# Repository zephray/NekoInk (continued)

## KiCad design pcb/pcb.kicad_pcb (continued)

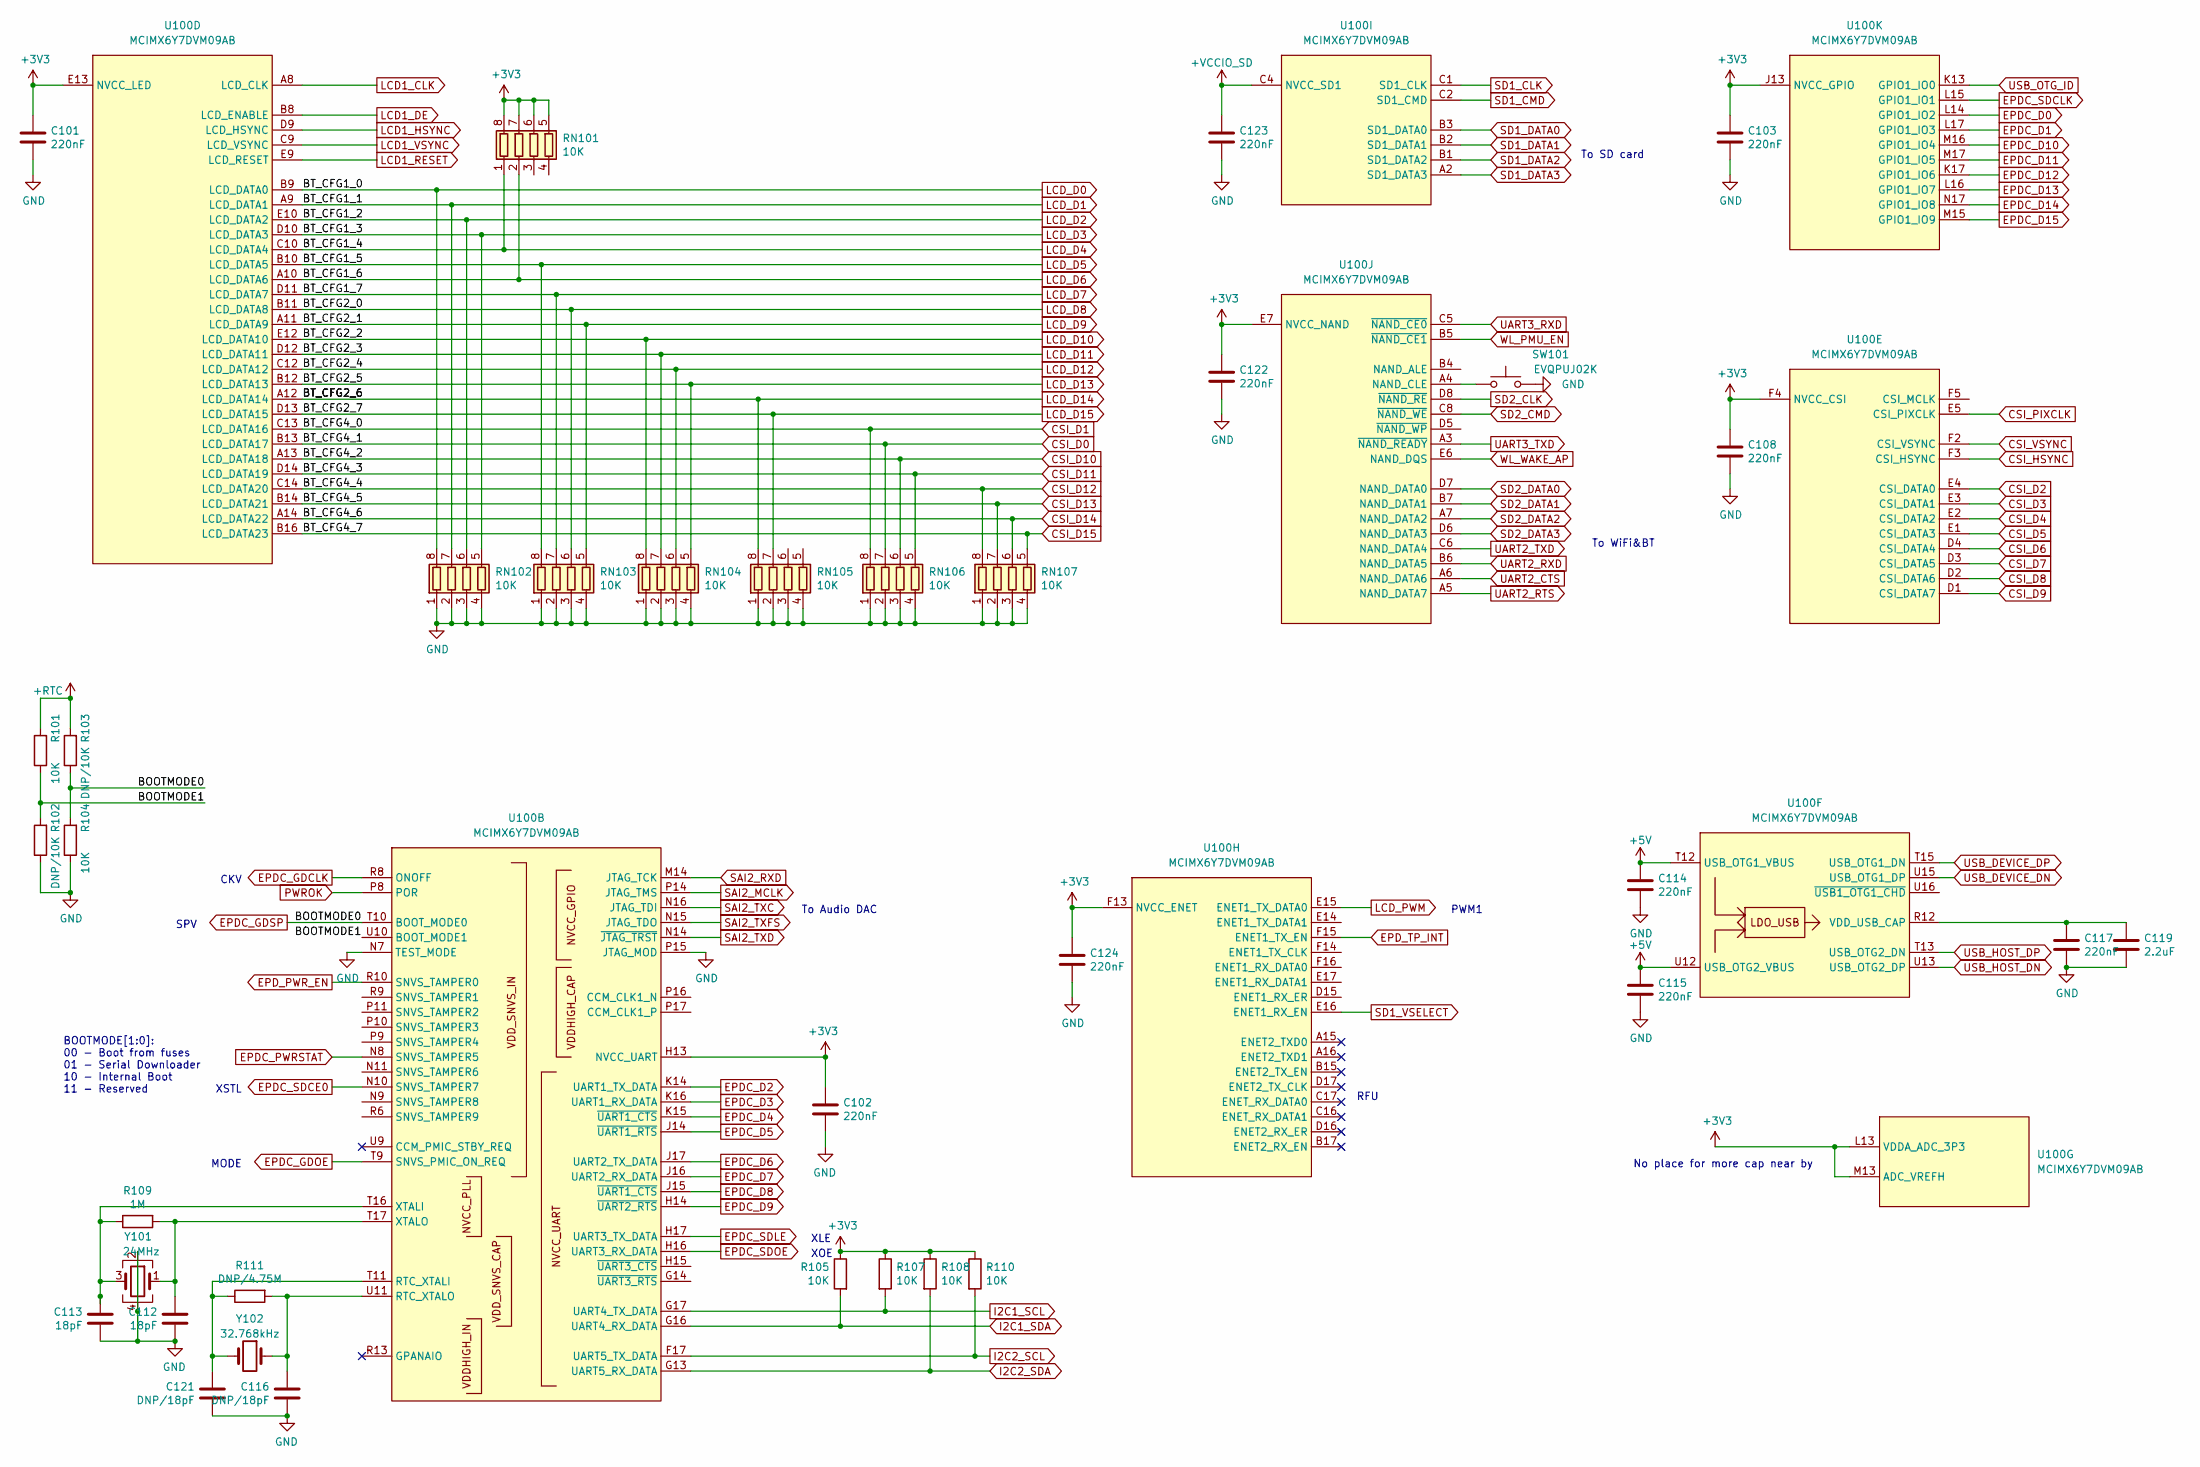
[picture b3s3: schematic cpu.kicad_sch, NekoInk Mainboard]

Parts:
C101, C102, C103, C108, C114, C115, C117, C122, C123, C124: 220nF; C_0402_1005Metric
C112, C113: 18pF; C_0402_1005Metric
C116, C121: DNP/18pF; C_0402_1005Metric
C119: 2.2uF; C_0402_1005Metric
R101, R104, R105, R107, R108, R110: 10K; R_0402_1005Metric
R102, R103: DNP/10K; R_0402_1005Metric
R109: 1M; R_0402_1005Metric
R111: DNP/4.75M; R_0402_1005Metric
RN101, RN102, RN103, RN104, RN105, RN106, RN107: 10K; R_Array_Convex_4x0402
SW101: EVQPUJ02K; Panasonic_EVQPUJ_EVQPUA
U100: MCIMX6Y7DVM09AB; BGA-289_17x17_14.0x14.0mm
Y101: 24MHz; Oscillator_SMD_Abracon_ASE-4Pin_3.2x2.5mm
Y102: 32.768kHz; Crystal_SMD_TXC_9HT11-2Pin_2.0x1.2mm_HandSoldering

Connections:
+5V: C114.1, C115.1, U100.T12 (USB_OTG1_VBUS), U100.U12 (USB_OTG2_VBUS); also elsewhere on the board
+RTC: R101.2, R103.2; also elsewhere on the board
/cpu/BOOTMODE1: R101.1, R102.2, U100.U10 (BOOT_MODE1)
CSI_D0: RN106.7 (R2.2), U100.B13 (LCD_DATA17); also elsewhere on the board
CSI_D1: RN106.8 (R1.2), U100.C13 (LCD_DATA16); also elsewhere on the board
CSI_D2: U100.E4 (CSI_DATA0); also elsewhere on the board
CSI_D3: U100.E3 (CSI_DATA1); also elsewhere on the board
CSI_D4: U100.E2 (CSI_DATA2); also elsewhere on the board
CSI_D5: U100.E1 (CSI_DATA3); also elsewhere on the board
CSI_D6: U100.D4 (CSI_DATA4); also elsewhere on the board
CSI_D7: U100.D3 (CSI_DATA5); also elsewhere on the board
CSI_D8: U100.D2 (CSI_DATA6); also elsewhere on the board
CSI_D9: U100.D1 (CSI_DATA7); also elsewhere on the board
CSI_D10: RN106.6 (R3.2), U100.A13 (LCD_DATA18); also elsewhere on the board
CSI_D11: RN106.5 (R4.2), U100.D14 (LCD_DATA19); also elsewhere on the board
CSI_D12: RN107.8 (R1.2), U100.C14 (LCD_DATA20); also elsewhere on the board
CSI_D13: RN107.7 (R2.2), U100.B14 (LCD_DATA21); also elsewhere on the board
CSI_D14: RN107.6 (R3.2), U100.A14 (LCD_DATA22); also elsewhere on the board
CSI_D15: RN107.5 (R4.2), U100.B16 (LCD_DATA23); also elsewhere on the board
CSI_HSYNC: U100.F3 (CSI_HSYNC); also elsewhere on the board
CSI_PIXCLK: U100.E5 (CSI_PIXCLK); also elsewhere on the board
CSI_VSYNC: U100.F2 (CSI_VSYNC); also elsewhere on the board
EPDC_D0: U100.L14 (GPIO1_IO2); also elsewhere on the board
EPDC_D1: U100.L17 (GPIO1_IO3); also elsewhere on the board
EPDC_D2: U100.K14 (UART1_TX_DATA); also elsewhere on the board
EPDC_D3: U100.K16 (UART1_RX_DATA); also elsewhere on the board
EPDC_D4: U100.K15 (~UART1_CTS); also elsewhere on the board
EPDC_D5: U100.J14 (~UART1_RTS); also elsewhere on the board
EPDC_D6: U100.J17 (UART2_TX_DATA); also elsewhere on the board
EPDC_D7: U100.J16 (UART2_RX_DATA); also elsewhere on the board
EPDC_D8: U100.J15 (~UART1_CTS); also elsewhere on the board
EPDC_D9: U100.H14 (~UART2_RTS); also elsewhere on the board
EPDC_D10: U100.M16 (GPIO1_IO4); also elsewhere on the board
EPDC_D11: U100.M17 (GPIO1_IO5); also elsewhere on the board
EPDC_D12: U100.K17 (GPIO1_IO6); also elsewhere on the board
EPDC_D13: U100.L16 (GPIO1_IO7); also elsewhere on the board
EPDC_D14: U100.N17 (GPIO1_IO8); also elsewhere on the board
EPDC_D15: U100.M15 (GPIO1_IO9); also elsewhere on the board
EPDC_GDCLK: U100.R8 (ONOFF); also elsewhere on the board
EPDC_GDOE: U100.T9 (SNVS_PMIC_ON_REQ); also elsewhere on the board
EPDC_GDSP: R103.1, R104.2, U100.T10 (BOOT_MODE0); also elsewhere on the board
EPDC_SDCE0: U100.N10 (SNVS_TAMPER7); also elsewhere on the board
EPDC_SDCLK: U100.L15 (GPIO1_IO1); also elsewhere on the board
EPDC_SDLE: U100.H17 (UART3_TX_DATA); also elsewhere on the board
EPDC_SDOE: U100.H16 (UART3_RX_DATA); also elsewhere on the board
EPD_PWR_EN: U100.R10 (SNVS_TAMPER0); also elsewhere on the board
EPD_TP_INT: U100.F15 (ENET1_TX_EN); also elsewhere on the board
GND: C101.2, C102.2, C103.2, C108.2, C112.2, C113.2, C114.2, C115.2, C116.2, C117.2, C119.2, C121.2, C122.2, C123.2, C124.2, R102.1, R104.1, RN102.1 (R1.1), RN102.2 (R2.1), RN102.3 (R3.1), RN102.4 (R4.1), RN103.1 (R1.1), RN103.2 (R2.1), RN103.3 (R3.1), RN103.4 (R4.1), RN104.1 (R1.1), RN104.2 (R2.1), RN104.3 (R3.1), RN104.4 (R4.1), RN105.1 (R1.1), RN105.2 (R2.1), RN105.3 (R3.1), RN105.4 (R4.1), RN106.1 (R1.1), RN106.2 (R2.1), RN106.3 (R3.1), RN106.4 (R4.1), RN107.1 (R1.1), RN107.2 (R2.1), RN107.3 (R3.1), RN107.4 (R4.1), SW101.2, U100.N7 (TEST_MODE), U100.P15 (JTAG_MOD), Y101.2, Y101.4; also elsewhere on the board
I2C1_SCL: R107.2, U100.G17 (UART4_TX_DATA); also elsewhere on the board
I2C1_SDA: R105.2, U100.G16 (UART4_RX_DATA); also elsewhere on the board
I2C2_SCL: R110.2, U100.F17 (UART5_TX_DATA)
I2C2_SDA: R108.2, U100.G13 (UART5_RX_DATA)
LCD1_CLK: U100.A8 (LCD_CLK); also elsewhere on the board
LCD1_DE: U100.B8 (LCD_ENABLE); also elsewhere on the board
LCD1_HSYNC: U100.D9 (LCD_HSYNC); also elsewhere on the board
LCD1_VSYNC: U100.C9 (LCD_VSYNC); also elsewhere on the board
LCD_D0: RN102.8 (R1.2), U100.B9 (LCD_DATA0); also elsewhere on the board
LCD_D1: RN102.7 (R2.2), U100.A9 (LCD_DATA1); also elsewhere on the board
LCD_D2: RN102.6 (R3.2), U100.E10 (LCD_DATA2); also elsewhere on the board
LCD_D3: RN102.5 (R4.2), U100.D10 (LCD_DATA3); also elsewhere on the board
LCD_D4: RN101.1 (R1.1), U100.C10 (LCD_DATA4); also elsewhere on the board
LCD_D5: RN103.8 (R1.2), U100.B10 (LCD_DATA5); also elsewhere on the board
LCD_D6: RN101.2 (R2.1), U100.A10 (LCD_DATA6); also elsewhere on the board
LCD_D7: RN103.7 (R2.2), U100.D11 (LCD_DATA7); also elsewhere on the board
LCD_D8: RN103.6 (R3.2), U100.B11 (LCD_DATA8); also elsewhere on the board
LCD_D9: RN103.5 (R4.2), U100.A11 (LCD_DATA9); also elsewhere on the board
LCD_D10: RN104.8 (R1.2), U100.E12 (LCD_DATA10); also elsewhere on the board
LCD_D11: RN104.7 (R2.2), U100.D12 (LCD_DATA11); also elsewhere on the board
LCD_D12: RN104.6 (R3.2), U100.C12 (LCD_DATA12); also elsewhere on the board
LCD_D13: RN104.5 (R4.2), U100.B12 (LCD_DATA13); also elsewhere on the board
LCD_D14: RN105.8 (R1.2), U100.A12 (LCD_DATA14); also elsewhere on the board
LCD_D15: RN105.7 (R2.2), U100.D13 (LCD_DATA15); also elsewhere on the board
LCD_PWM: U100.E15 (ENET1_TX_DATA0); also elsewhere on the board
unnamed: C112.1, R109.2, U100.T17 (XTALO), Y101.1
unnamed: C113.1, R109.1, U100.T16 (XTALI), Y101.3
unnamed: C116.1, R111.2, U100.U11 (RTC_XTALO), Y102.1
unnamed: C117.1, C119.1, U100.R12 (VDD_USB_CAP)
unnamed: C121.1, R111.1, U100.T11 (RTC_XTALI), Y102.2
unnamed: SW101.1, U100.A4 (NAND_CLE)
PWROK: U100.P8 (POR); also elsewhere on the board
SAI2_MCLK: U100.P14 (JTAG_TMS); also elsewhere on the board
SAI2_RXD: U100.M14 (JTAG_TCK); also elsewhere on the board
SAI2_TXC: U100.N16 (JTAG_TDI); also elsewhere on the board
SAI2_TXD: U100.N14 (~JTAG_TRST); also elsewhere on the board
SAI2_TXFS: U100.N15 (JTAG_TDO); also elsewhere on the board
SD1_CLK: U100.C1 (SD1_CLK); also elsewhere on the board
SD1_CMD: U100.C2 (SD1_CMD); also elsewhere on the board
SD1_DATA0: U100.B3 (SD1_DATA0); also elsewhere on the board
SD1_DATA1: U100.B2 (SD1_DATA1); also elsewhere on the board
SD1_DATA2: U100.B1 (SD1_DATA2); also elsewhere on the board
SD1_DATA3: U100.A2 (SD1_DATA3); also elsewhere on the board
SD2_CLK: U100.D8 (~NAND_RE); also elsewhere on the board
SD2_CMD: U100.C8 (~NAND_WE); also elsewhere on the board
SD2_DATA0: U100.D7 (NAND_DATA0); also elsewhere on the board
SD2_DATA1: U100.B7 (NAND_DATA1); also elsewhere on the board
SD2_DATA2: U100.A7 (NAND_DATA2); also elsewhere on the board
SD2_DATA3: U100.D6 (NAND_DATA3); also elsewhere on the board
UART2_CTS: U100.A6 (NAND_DATA6); also elsewhere on the board
UART2_RTS: U100.A5 (NAND_DATA7); also elsewhere on the board
UART2_RXD: U100.B6 (NAND_DATA5); also elsewhere on the board
UART2_TXD: U100.C6 (NAND_DATA4); also elsewhere on the board
UART3_RXD: U100.C5 (~NAND_CE0); also elsewhere on the board
UART3_TXD: U100.A3 (~NAND_READY); also elsewhere on the board
USB_DEVICE_DN: U100.U15 (USB_OTG1_DP); also elsewhere on the board
USB_DEVICE_DP: U100.T15 (USB_OTG1_DN); also elsewhere on the board
USB_HOST_DN: U100.U13 (USB_OTG2_DP); also elsewhere on the board
USB_HOST_DP: U100.T13 (USB_OTG2_DN); also elsewhere on the board
WL_PMU_EN: U100.B5 (~NAND_CE1); also elsewhere on the board
WL_WAKE_AP: U100.E6 (NAND_DQS); also elsewhere on the board

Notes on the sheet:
BOOTMODE[1:0]: 00 - Boot from fuses 01 - Serial Downloader 10 - Internal Boot 11 - Reserved
SPV
CKV
XSTL
MODE
XLE
XOE
To Audio DAC
RFU
PWM1
To SD card
No place for more cap near by
To WiFi&BT

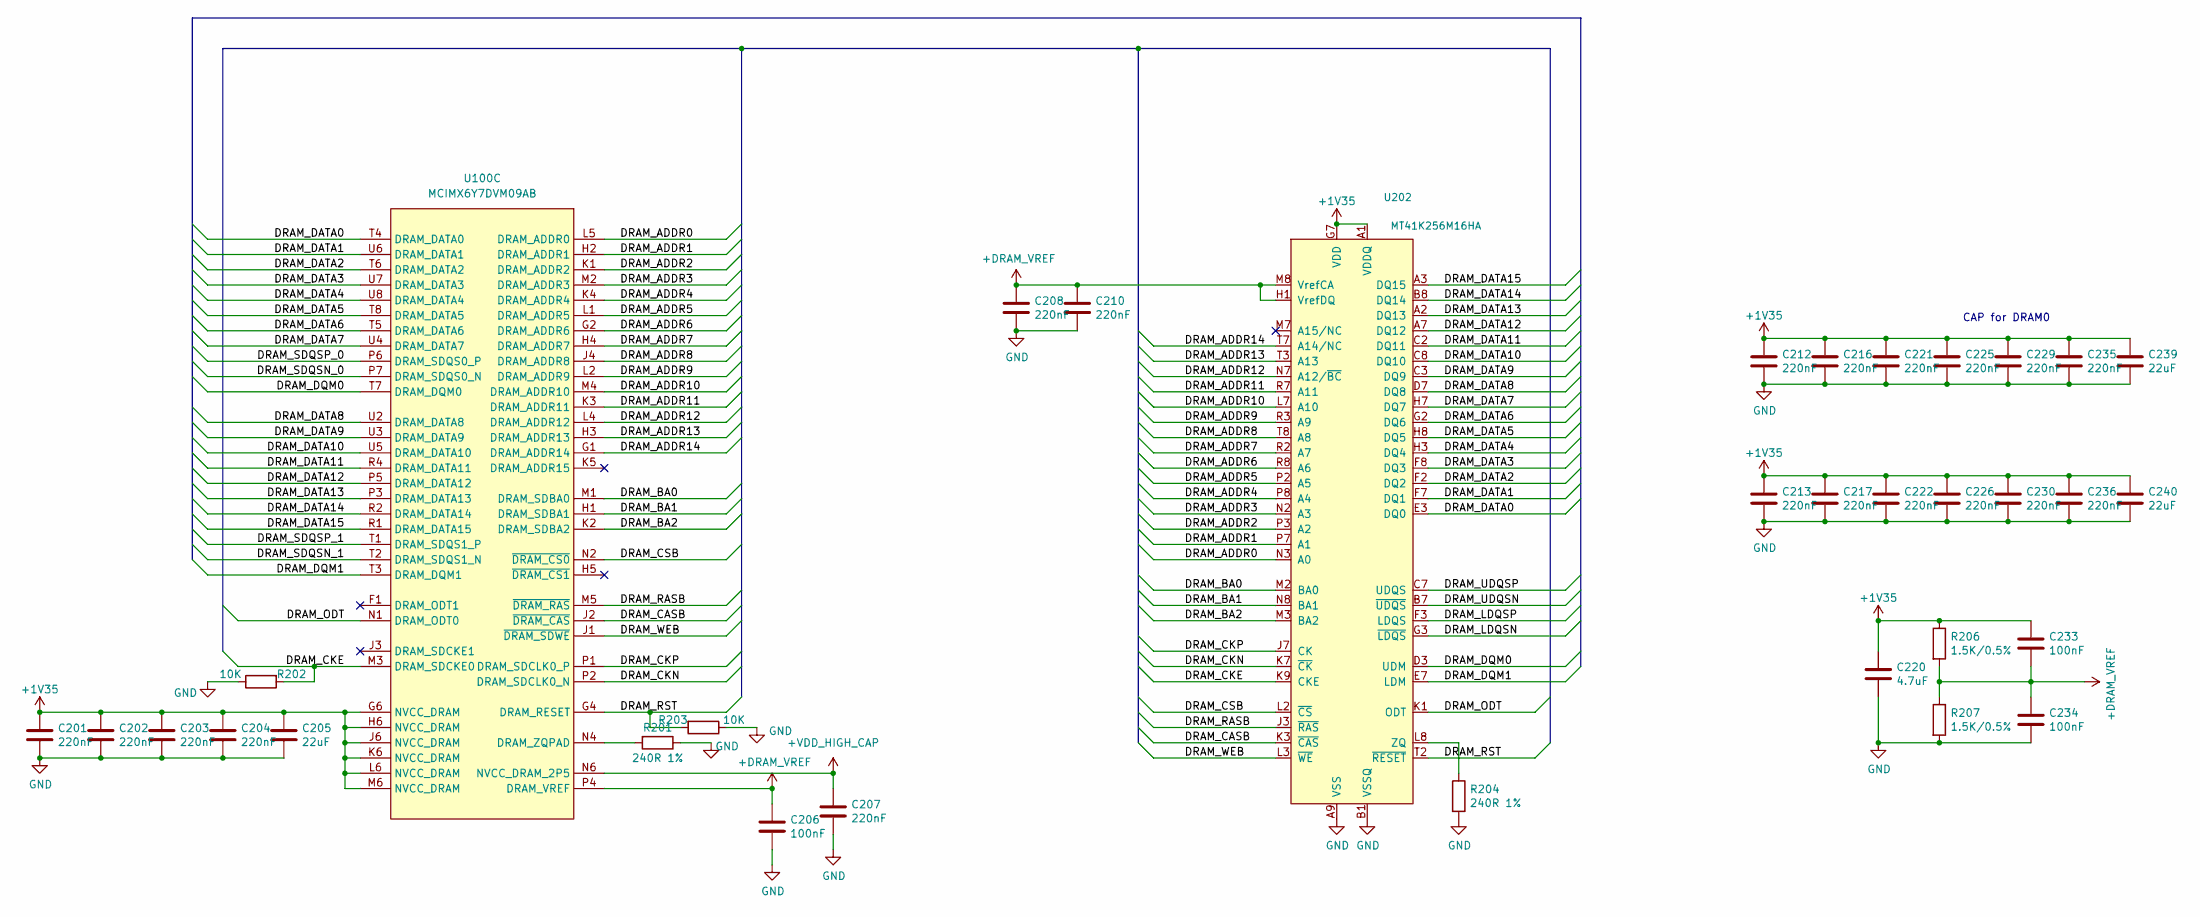
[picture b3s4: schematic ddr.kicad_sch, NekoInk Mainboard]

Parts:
C201, C202, C203, C204, C207, C208, C210, C212, C213, C216, C217, C221, C222, C225, C226, C229, C230, C235, C236: 220nF; C_0402_1005Metric
C205, C239, C240: 22uF; C_0603_1608Metric
C206, C233, C234: 100nF; C_0402_1005Metric
C220: 4.7uF; C_0603_1608Metric
R201, R204: 240R 1%; R_0402_1005Metric
R202, R203: 10K; R_0402_1005Metric
R206, R207: 1.5K/0.5%; R_0402_1005Metric
U100: MCIMX6Y7DVM09AB; BGA-289_17x17_14.0x14.0mm
U202: MT41K256M16HA; BGA-96_9.0x13.0mm_P0.8mm

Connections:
+1V35: C201.1, C202.1, C203.1, C204.1, C205.1, C212.1, C213.1, C216.1, C217.1, C220.1, C221.1, C222.1, C225.1, C226.1, C229.1, C230.1, C233.1, C235.1, C236.1, C239.1, C240.1, R206.1, U100.G6 (NVCC_DRAM), U100.H6 (NVCC_DRAM), U100.J6 (NVCC_DRAM), U100.K6 (NVCC_DRAM), U100.L6 (NVCC_DRAM), U100.M6 (NVCC_DRAM), U202.A1 (VDDQ), U202.A8 (VDDQ), U202.B2 (VDD), U202.C1 (VDDQ), U202.C9 (VDDQ), U202.D2 (VDDQ), U202.D9 (VDD), U202.E9 (VDDQ), U202.F1 (VDDQ), U202.G7 (VDD), U202.H2 (VDDQ), U202.H9 (VDDQ), U202.K2 (VDD), U202.K8 (VDD), U202.N1 (VDD), U202.N9 (VDD), U202.R1 (VDD), U202.R9 (VDD); also elsewhere on the board
+DRAM_VREF: C206.1, C208.1, C210.1, C233.2, C234.1, R206.2, R207.1, U100.P4 (DRAM_VREF), U202.H1 (VrefDQ), U202.M8 (VrefCA)
+VDD_HIGH_CAP: C207.1, U100.N6 (NVCC_DRAM_2P5)
/ddr/DRAM_ADDR0: U100.L5 (DRAM_ADDR0), U202.N3 (A0)
/ddr/DRAM_ADDR1: U100.H2 (DRAM_ADDR1), U202.P7 (A1)
/ddr/DRAM_ADDR2: U100.K1 (DRAM_ADDR2), U202.P3 (A2)
/ddr/DRAM_ADDR3: U100.M2 (DRAM_ADDR3), U202.N2 (A3)
/ddr/DRAM_ADDR4: U100.K4 (DRAM_ADDR4), U202.P8 (A4)
/ddr/DRAM_ADDR5: U100.L1 (DRAM_ADDR5), U202.P2 (A5)
/ddr/DRAM_ADDR6: U100.G2 (DRAM_ADDR6), U202.R8 (A6)
/ddr/DRAM_ADDR7: U100.H4 (DRAM_ADDR7), U202.R2 (A7)
/ddr/DRAM_ADDR8: U100.J4 (DRAM_ADDR8), U202.T8 (A8)
/ddr/DRAM_ADDR9: U100.L2 (DRAM_ADDR9), U202.R3 (A9)
/ddr/DRAM_ADDR10: U100.M4 (DRAM_ADDR10), U202.L7 (A10)
/ddr/DRAM_ADDR11: U100.K3 (DRAM_ADDR11), U202.R7 (A11)
/ddr/DRAM_ADDR12: U100.L4 (DRAM_ADDR12), U202.N7 (A12/~BC)
/ddr/DRAM_ADDR13: U100.H3 (DRAM_ADDR13), U202.T3 (A13)
/ddr/DRAM_ADDR14: U100.G1 (DRAM_ADDR14), U202.T7 (A14/NC)
/ddr/DRAM_BA0: U100.M1 (DRAM_SDBA0), U202.M2 (BA0)
/ddr/DRAM_BA1: U100.H1 (DRAM_SDBA1), U202.N8 (BA1)
/ddr/DRAM_BA2: U100.K2 (DRAM_SDBA2), U202.M3 (BA2)
/ddr/DRAM_CASB: U100.J2 (~DRAM_CAS), U202.K3 (~CAS)
/ddr/DRAM_CKE: R202.2, U100.M3 (DRAM_SDCKE0), U202.K9 (CKE)
/ddr/DRAM_CKN: U100.P2 (DRAM_SDCLK0_N), U202.K7 (~CK)
/ddr/DRAM_CKP: U100.P1 (DRAM_SDCLK0_P), U202.J7 (CK)
/ddr/DRAM_CSB: U100.N2 (~DRAM_CS0), U202.L2 (~CS)
/ddr/DRAM_DATA0: U100.T4 (DRAM_DATA0), U202.E3 (DQ0)
/ddr/DRAM_DATA1: U100.U6 (DRAM_DATA1), U202.F7 (DQ1)
/ddr/DRAM_DATA2: U100.T6 (DRAM_DATA2), U202.F2 (DQ2)
/ddr/DRAM_DATA3: U100.U7 (DRAM_DATA3), U202.F8 (DQ3)
/ddr/DRAM_DATA4: U100.U8 (DRAM_DATA4), U202.H3 (DQ4)
/ddr/DRAM_DATA5: U100.T8 (DRAM_DATA5), U202.H8 (DQ5)
/ddr/DRAM_DATA6: U100.T5 (DRAM_DATA6), U202.G2 (DQ6)
/ddr/DRAM_DATA7: U100.U4 (DRAM_DATA7), U202.H7 (DQ7)
/ddr/DRAM_DATA8: U100.U2 (DRAM_DATA8), U202.D7 (DQ8)
/ddr/DRAM_DATA9: U100.U3 (DRAM_DATA9), U202.C3 (DQ9)
/ddr/DRAM_DATA10: U100.U5 (DRAM_DATA10), U202.C8 (DQ10)
/ddr/DRAM_DATA11: U100.R4 (DRAM_DATA11), U202.C2 (DQ11)
/ddr/DRAM_DATA12: U100.P5 (DRAM_DATA12), U202.A7 (DQ12)
/ddr/DRAM_DATA13: U100.P3 (DRAM_DATA13), U202.A2 (DQ13)
/ddr/DRAM_DATA14: U100.R2 (DRAM_DATA14), U202.B8 (DQ14)
/ddr/DRAM_DATA15: U100.R1 (DRAM_DATA15), U202.A3 (DQ15)
/ddr/DRAM_DQM0: U100.T7 (DRAM_DQM0), U202.D3 (UDM)
/ddr/DRAM_DQM1: U100.T3 (DRAM_DQM1), U202.E7 (LDM)
/ddr/DRAM_ODT: U100.N1 (DRAM_ODT0), U202.K1 (ODT)
/ddr/DRAM_RASB: U100.M5 (~DRAM_RAS), U202.J3 (~RAS)
/ddr/DRAM_RST: R203.2, U100.G4 (DRAM_RESET), U202.T2 (~RESET)
/ddr/DRAM_WEB: U100.J1 (~DRAM_SDWE), U202.L3 (~WE)
GND: C201.2, C202.2, C203.2, C204.2, C205.2, C206.2, C207.2, C208.2, C210.2, C212.2, C213.2, C216.2, C217.2, C220.2, C221.2, C222.2, C225.2, C226.2, C229.2, C230.2, C234.2, C235.2, C236.2, C239.2, C240.2, R201.1, R202.1, R203.1, R204.2, R207.2, U202.A9 (VSS), U202.B1 (VSSQ), U202.B3 (VSS), U202.B9 (VSSQ), U202.D1 (VSSQ), U202.D8 (VSSQ), U202.E1 (VSS), U202.E2 (VSSQ), U202.E8 (VSSQ), U202.F9 (VSSQ), U202.G1 (VSSQ), U202.G8 (VSS), U202.G9 (VSSQ), U202.J2 (VSS), U202.J8 (VSS), U202.M1 (VSS), U202.M9 (VSS), U202.P1 (VSS), U202.P9 (VSS), U202.T1 (VSS), U202.T9 (VSS); also elsewhere on the board
unnamed: R201.2, U100.N4 (DRAM_ZQPAD)
unnamed: R204.1, U202.L8 (ZQ)

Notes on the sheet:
CAP for DRAM0

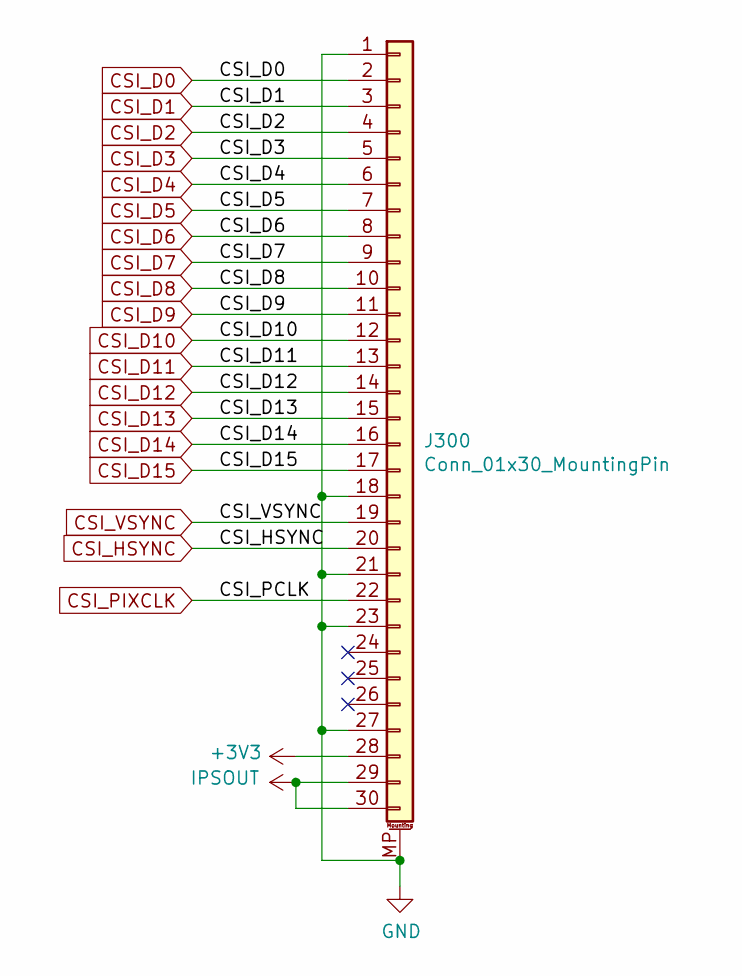
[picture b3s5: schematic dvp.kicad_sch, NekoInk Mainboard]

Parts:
J300: Conn_01x30_MountingPin; TE_3-1734839-0_1x30-1MP_P0.5mm_Horizontal

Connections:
CSI_D0: J300.2; also elsewhere on the board
CSI_D1: J300.3; also elsewhere on the board
CSI_D2: J300.4; also elsewhere on the board
CSI_D3: J300.5; also elsewhere on the board
CSI_D4: J300.6; also elsewhere on the board
CSI_D5: J300.7; also elsewhere on the board
CSI_D6: J300.8; also elsewhere on the board
CSI_D7: J300.9; also elsewhere on the board
CSI_D8: J300.10; also elsewhere on the board
CSI_D9: J300.11; also elsewhere on the board
CSI_D10: J300.12; also elsewhere on the board
CSI_D11: J300.13; also elsewhere on the board
CSI_D12: J300.14; also elsewhere on the board
CSI_D13: J300.15; also elsewhere on the board
CSI_D14: J300.16; also elsewhere on the board
CSI_D15: J300.17; also elsewhere on the board
CSI_HSYNC: J300.20; also elsewhere on the board
CSI_PIXCLK: J300.22; also elsewhere on the board
CSI_VSYNC: J300.19; also elsewhere on the board
GND: J300.1, J300.18, J300.21, J300.23, J300.27, J300.MP (MountPin); also elsewhere on the board
IPSOUT: J300.29, J300.30; also elsewhere on the board

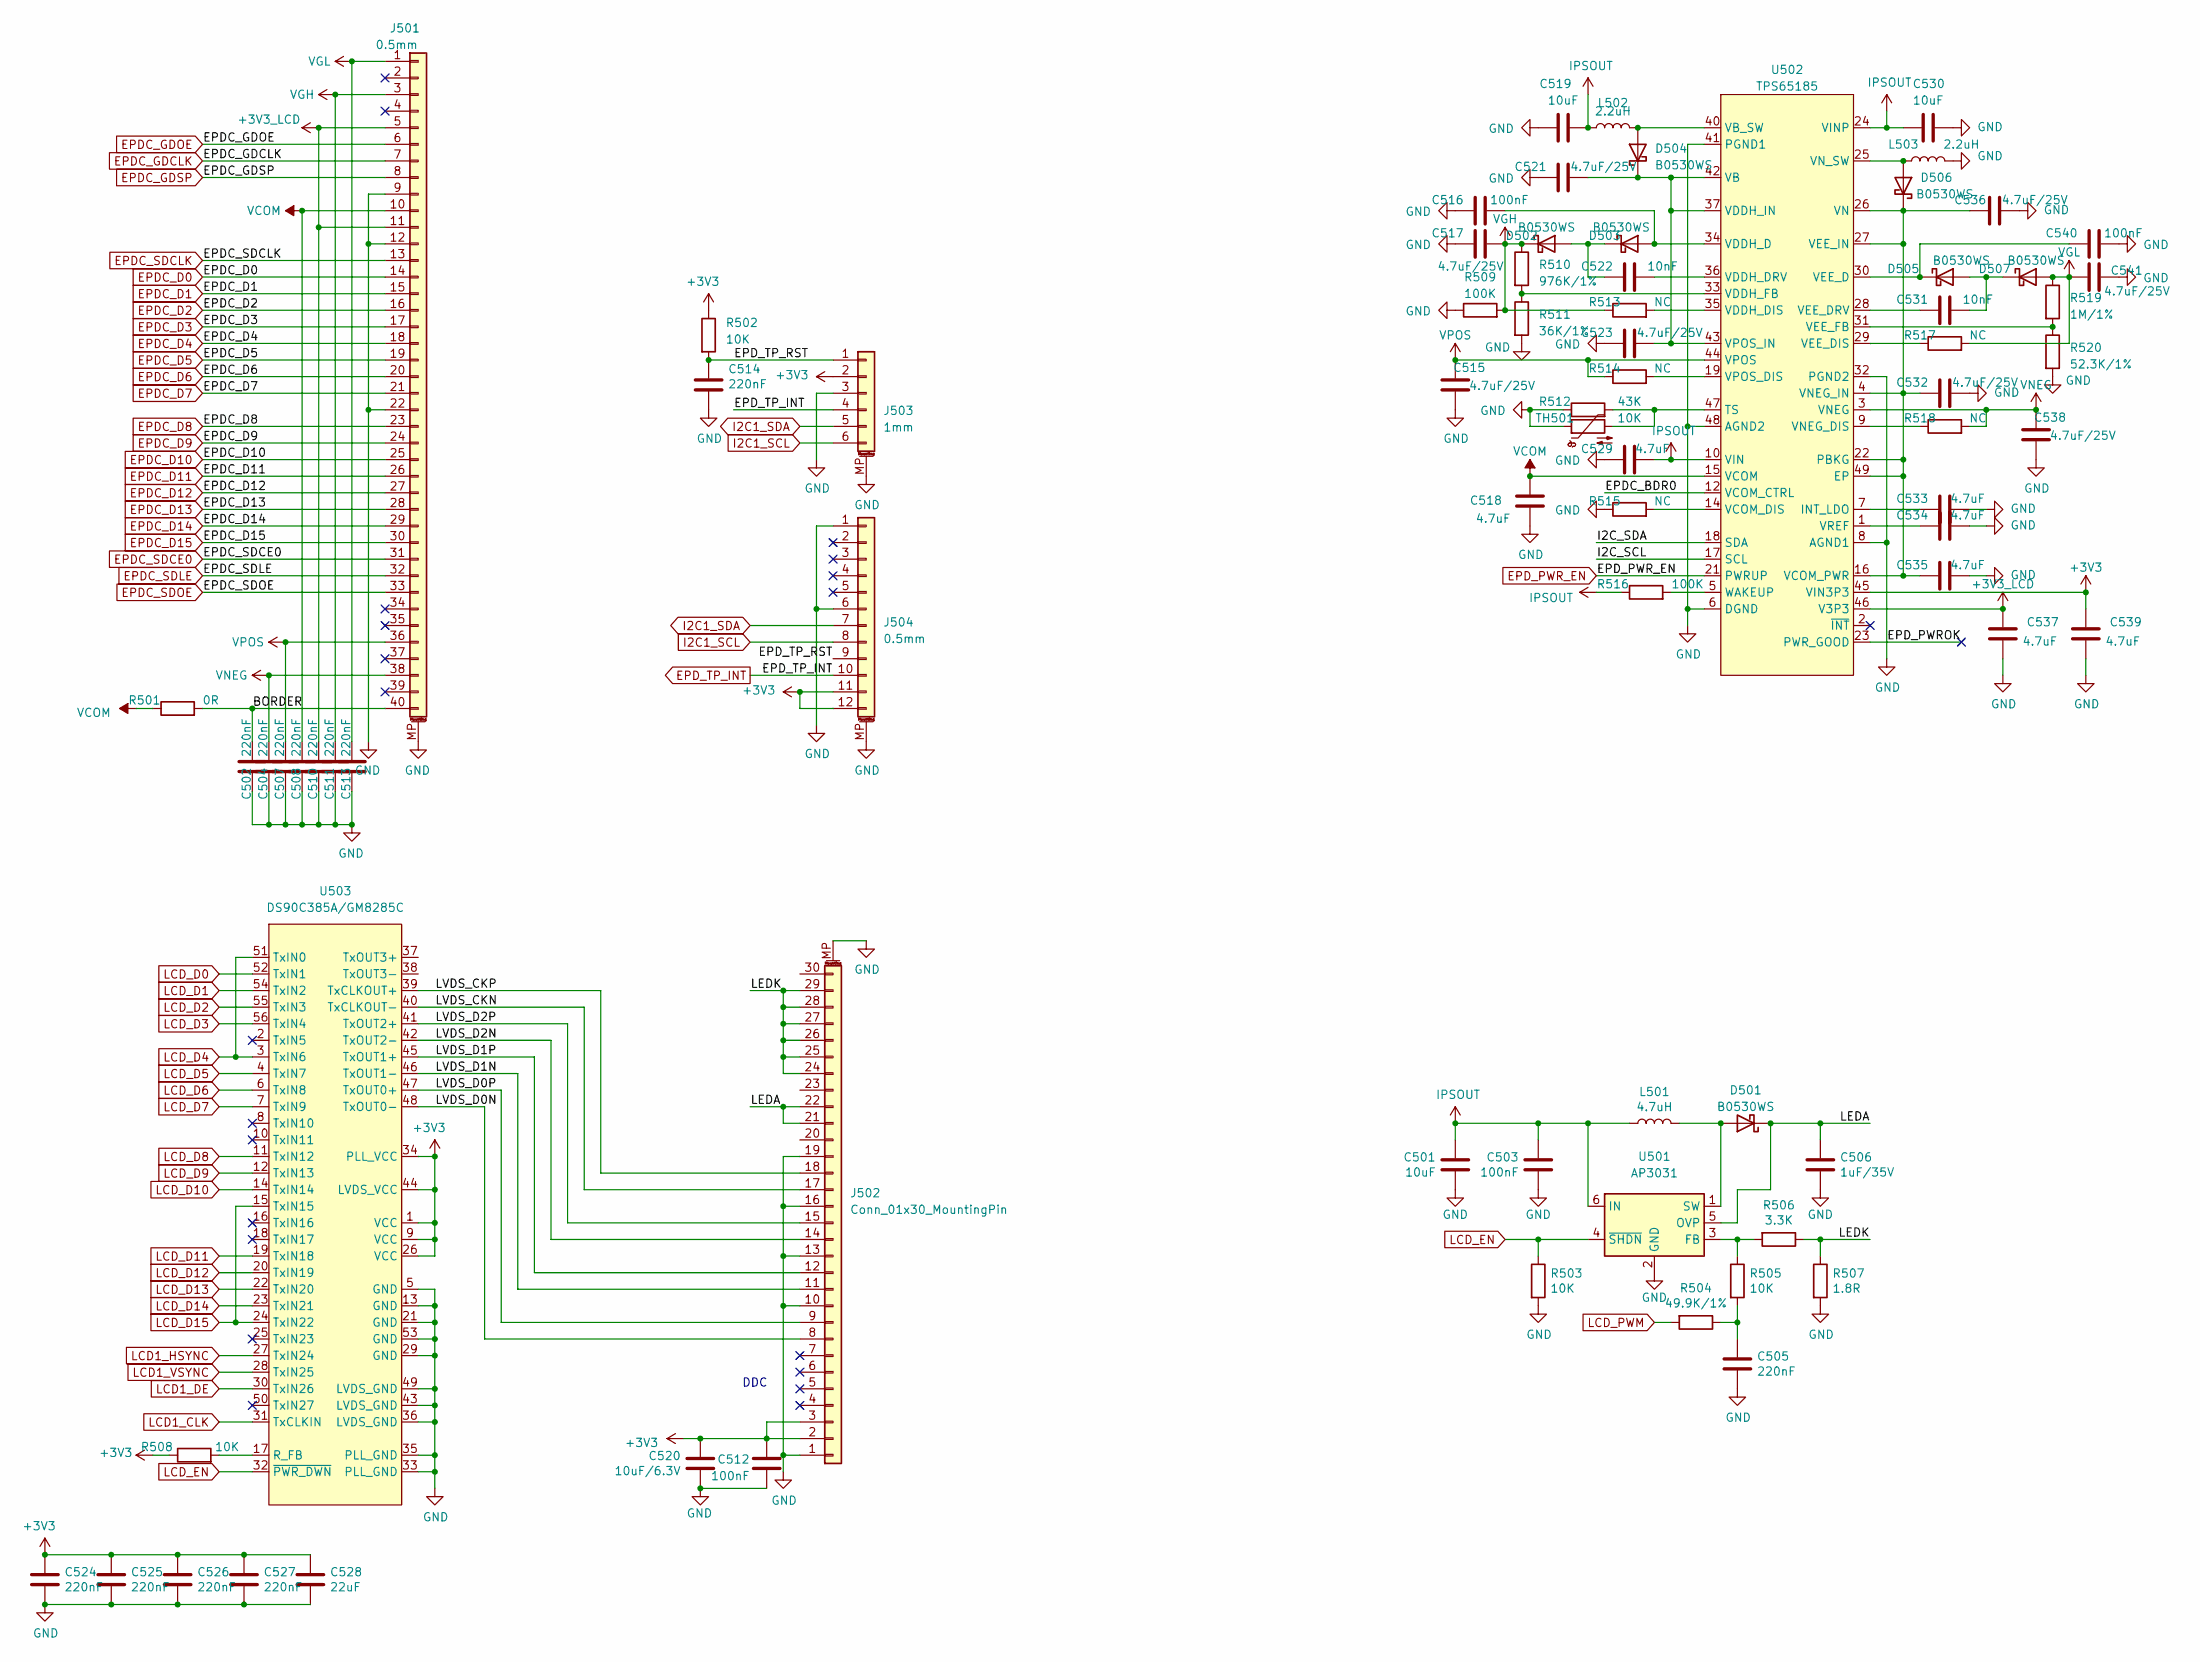
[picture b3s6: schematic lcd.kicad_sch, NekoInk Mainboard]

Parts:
C501, C519, C530: 10uF; C_0603_1608Metric
C502, C504, C505, C507, C508, C510, C511, C513, C514, C524, C525, C526, C527: 220nF; C_0402_1005Metric
C503, C512, C516, C540: 100nF; C_0402_1005Metric
C506: 1uF/35V; C_0603_1608Metric
C515, C517, C521, C523, C532, C536, C538, C541: 4.7uF/25V; C_0805_2012Metric
C518, C529, C533, C534, C535, C537, C539: 4.7uF; C_0603_1608Metric
C520: 10uF/6.3V; C_0603_1608Metric
C522, C531: 10nF; C_0402_1005Metric
C528: 22uF; C_0603_1608Metric
D501, D502, D503, D504, D505, D506, D507: B0530WS; D_SOD-323
J501: 0.5mm; Hirose_FH12-40S-0.5SH_1x40-1MP_P0.50mm_Horizontal_Reversed
J502: Conn_01x30_MountingPin; Hirose_FH12-30S-0.5SH_1x30-1MP_P0.50mm_Horizontal_Reversed
J503: 1mm; Molex_200528-0060_1x06-1MP_P1.00mm_Horizontal_Reversed
J504: 0.5mm; Hirose_FH12-12S-0.5SH_1x12-1MP_P0.50mm_Horizontal_Reversed
L501: 4.7uH; L_1212
L502, L503: 2.2uH; L_1212
R501: 0R; R_0402_1005Metric
R502, R503, R505, R508: 10K; R_0402_1005Metric
R504: 49.9K/1%; R_0402_1005Metric
R506: 3.3K; R_0402_1005Metric
R507: 1.8R; R_0402_1005Metric
R509, R516: 100K; R_0402_1005Metric
R510: 976K/1%; R_0402_1005Metric
R511: 36K/1%; R_0402_1005Metric
R512: 43K; R_0402_1005Metric
R513, R514, R515, R517, R518: NC; R_0402_1005Metric
R519: 1M/1%; R_0402_1005Metric
R520: 52.3K/1%; R_0402_1005Metric
TH501: 10K; R_0402_1005Metric
U501: AP3031; SOT-23-6
U502: TPS65185; QFN-48-1EP_6x6mm_P0.4mm_EP4.2x4.2mm_ThermalVias
U503: DS90C385A/GM8285C; TSSOP-56_6.1x14mm_P0.5mm

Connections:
+3V3_LCD: C510.1, C537.1, J501.5, J501.11, U502.46 (V3P3)
/lcd/BORDER: C502.1, J501.40, R501.2
/lcd/EPD_TP_RST: C514.1, J503.1, J504.9, R502.2
/lcd/LEDA: C506.2, D501.1 (K), J502.21, J502.22, U501.5 (OVP)
/lcd/LEDK: J502.24, J502.25, J502.26, J502.27, J502.28, J502.29, R506.1, R507.1
/lcd/LVDS_CKN: J502.17, U503.40 (TxCLKOUT-)
/lcd/LVDS_CKP: J502.18, U503.39 (TxCLKOUT+)
/lcd/LVDS_D0N: J502.8, U503.48 (TxOUT0-)
/lcd/LVDS_D0P: J502.9, U503.47 (TxOUT0+)
/lcd/LVDS_D1N: J502.11, U503.46 (TxOUT1-)
/lcd/LVDS_D1P: J502.12, U503.45 (TxOUT1+)
/lcd/LVDS_D2N: J502.14, U503.42 (TxOUT2-)
/lcd/LVDS_D2P: J502.15, U503.41 (TxOUT2+)
EPDC_D0: J501.14; also elsewhere on the board
EPDC_D1: J501.15; also elsewhere on the board
EPDC_D2: J501.16; also elsewhere on the board
EPDC_D3: J501.17; also elsewhere on the board
EPDC_D4: J501.18; also elsewhere on the board
EPDC_D5: J501.19; also elsewhere on the board
EPDC_D6: J501.20; also elsewhere on the board
EPDC_D7: J501.21; also elsewhere on the board
EPDC_D8: J501.23; also elsewhere on the board
EPDC_D9: J501.24; also elsewhere on the board
EPDC_D10: J501.25; also elsewhere on the board
EPDC_D11: J501.26; also elsewhere on the board
EPDC_D12: J501.27; also elsewhere on the board
EPDC_D13: J501.28; also elsewhere on the board
EPDC_D14: J501.29; also elsewhere on the board
EPDC_D15: J501.30; also elsewhere on the board
EPDC_GDCLK: J501.7; also elsewhere on the board
EPDC_GDOE: J501.6; also elsewhere on the board
EPDC_GDSP: J501.8; also elsewhere on the board
EPDC_SDCE0: J501.31; also elsewhere on the board
EPDC_SDCLK: J501.13; also elsewhere on the board
EPDC_SDLE: J501.32; also elsewhere on the board
EPDC_SDOE: J501.33; also elsewhere on the board
EPD_PWR_EN: U502.21 (PWRUP); also elsewhere on the board
EPD_TP_INT: J503.4, J504.10; also elsewhere on the board
GND: C501.1, C502.2, C503.1, C504.2, C505.1, C506.1, C507.2, C508.2, C510.2, C511.2, C512.2, C513.2, C514.2, C515.1, C516.1, C517.1, C518.1, C519.1, C520.2, C521.1, C523.1, C524.2, C525.2, C526.2, C527.2, C528.2, C529.1, C530.2, C532.2, C533.2, C534.2, C535.2, C536.2, C537.2, C538.1, C539.2, C540.2, C541.1, J501.9, J501.12, J501.22, J501.MP (MountPin), J502.1, J502.10, J502.13, J502.16, J502.19, J502.MP (MountPin), J503.3, J503.MP (MountPin), J504.1, J504.6, J504.MP (MountPin), L503.2, R503.2, R507.2, R509.1, R511.2, R512.1, R515.1, R520.2, TH501.1, U501.2 (GND), U502.6 (DGND), U502.8 (AGND1), U502.32 (PGND2), U502.41 (PGND1), U502.48 (AGND2), U503.5 (GND), U503.13 (GND), U503.21 (GND), U503.29 (GND), U503.33 (PLL_GND), U503.35 (PLL_GND), U503.36 (LVDS_GND), U503.43 (LVDS_GND), U503.49 (LVDS_GND), U503.53 (GND); also elsewhere on the board
I2C1_SCL: J503.6, J504.8; also elsewhere on the board
I2C1_SDA: J503.5, J504.7; also elsewhere on the board
IPSOUT: C501.2, C503.2, C519.2, C529.2, C530.1, L501.1, L502.1, R516.1, U501.6 (IN), U502.10 (VIN), U502.24 (VINP); also elsewhere on the board
LCD1_CLK: U503.31 (TxCLKIN); also elsewhere on the board
LCD1_DE: U503.30 (TxIN26); also elsewhere on the board
LCD1_HSYNC: U503.27 (TxIN24); also elsewhere on the board
LCD1_VSYNC: U503.28 (TxIN25); also elsewhere on the board
LCD_D0: U503.52 (TxIN1); also elsewhere on the board
LCD_D1: U503.54 (TxIN2); also elsewhere on the board
LCD_D2: U503.55 (TxIN3); also elsewhere on the board
LCD_D3: U503.56 (TxIN4); also elsewhere on the board
LCD_D4: U503.3 (TxIN6), U503.51 (TxIN0); also elsewhere on the board
LCD_D5: U503.4 (TxIN7); also elsewhere on the board
LCD_D6: U503.6 (TxIN8); also elsewhere on the board
LCD_D7: U503.7 (TxIN9); also elsewhere on the board
LCD_D8: U503.11 (TxIN12); also elsewhere on the board
LCD_D9: U503.12 (TxIN13); also elsewhere on the board
LCD_D10: U503.14 (TxIN14); also elsewhere on the board
LCD_D11: U503.19 (TxIN18); also elsewhere on the board
LCD_D12: U503.20 (TxIN19); also elsewhere on the board
LCD_D13: U503.22 (TxIN20); also elsewhere on the board
LCD_D14: U503.23 (TxIN21); also elsewhere on the board
LCD_D15: U503.15 (TxIN15), U503.24 (TxIN22); also elsewhere on the board
LCD_EN: R503.1, U501.4 (~SHDN), U503.32 (~PWR_DWN)
LCD_PWM: R504.2; also elsewhere on the board
unnamed: C505.2, R504.1, R505.2
unnamed: C516.2, D503.2 (A), U502.34 (VDDH_D)
unnamed: C521.2, C523.2, D504.1 (K), U502.37 (VDDH_IN), U502.42 (VB), U502.43 (VPOS_IN)
unnamed: C522.1, D502.2 (A), D503.1 (K)
unnamed: C522.2, U502.36 (VDDH_DRV)
unnamed: C531.1, U502.28 (VEE_DRV)
unnamed: C531.2, D505.2 (A), D507.1 (K)
unnamed: C532.1, C535.1, C536.1, D506.1 (K), U502.4 (VNEG_IN), U502.16 (VCOM_PWR), U502.22 (PBKG), U502.26 (VN), U502.27 (VEE_IN), U502.49 (EP)
unnamed: C533.1, U502.7 (INT_LDO)
unnamed: C534.1, U502.1 (VREF)
unnamed: C540.1, D505.1 (K), U502.30 (VEE_D)
unnamed: D501.2 (A), L501.2, U501.1 (SW)
unnamed: D504.2 (A), L502.2, U502.40 (VB_SW)
unnamed: D506.2 (A), L503.1, U502.25 (VN_SW)
unnamed: R505.1, R506.2, U501.3 (FB)
unnamed: R508.2, U503.17 (R_FB)
unnamed: R510.2, R511.1, U502.33 (VDDH_FB)
unnamed: R512.2, TH501.2, U502.47 (TS)
unnamed: R513.2, U502.35 (VDDH_DIS)
unnamed: R514.2, U502.19 (VPOS_DIS)
unnamed: R515.2, U502.14 (VCOM_DIS)
unnamed: R516.2, U502.5 (WAKEUP)
unnamed: R517.1, U502.29 (VEE_DIS)
unnamed: R518.1, U502.9 (VNEG_DIS)
unnamed: R519.2, R520.1, U502.31 (VEE_FB)
VCOM: C508.1, C518.2, J501.10, R501.1, U502.15 (VCOM)
VGH: C511.1, C517.2, D502.1 (K), J501.3, R509.2, R510.1, R513.1
VGL: C513.1, C541.2, D507.2 (A), J501.1, R517.2, R519.1
VNEG: C504.1, C538.2, J501.38, R518.2, U502.3 (VNEG)
VPOS: C507.1, C515.2, J501.36, R514.1, U502.44 (VPOS)

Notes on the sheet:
DDC
